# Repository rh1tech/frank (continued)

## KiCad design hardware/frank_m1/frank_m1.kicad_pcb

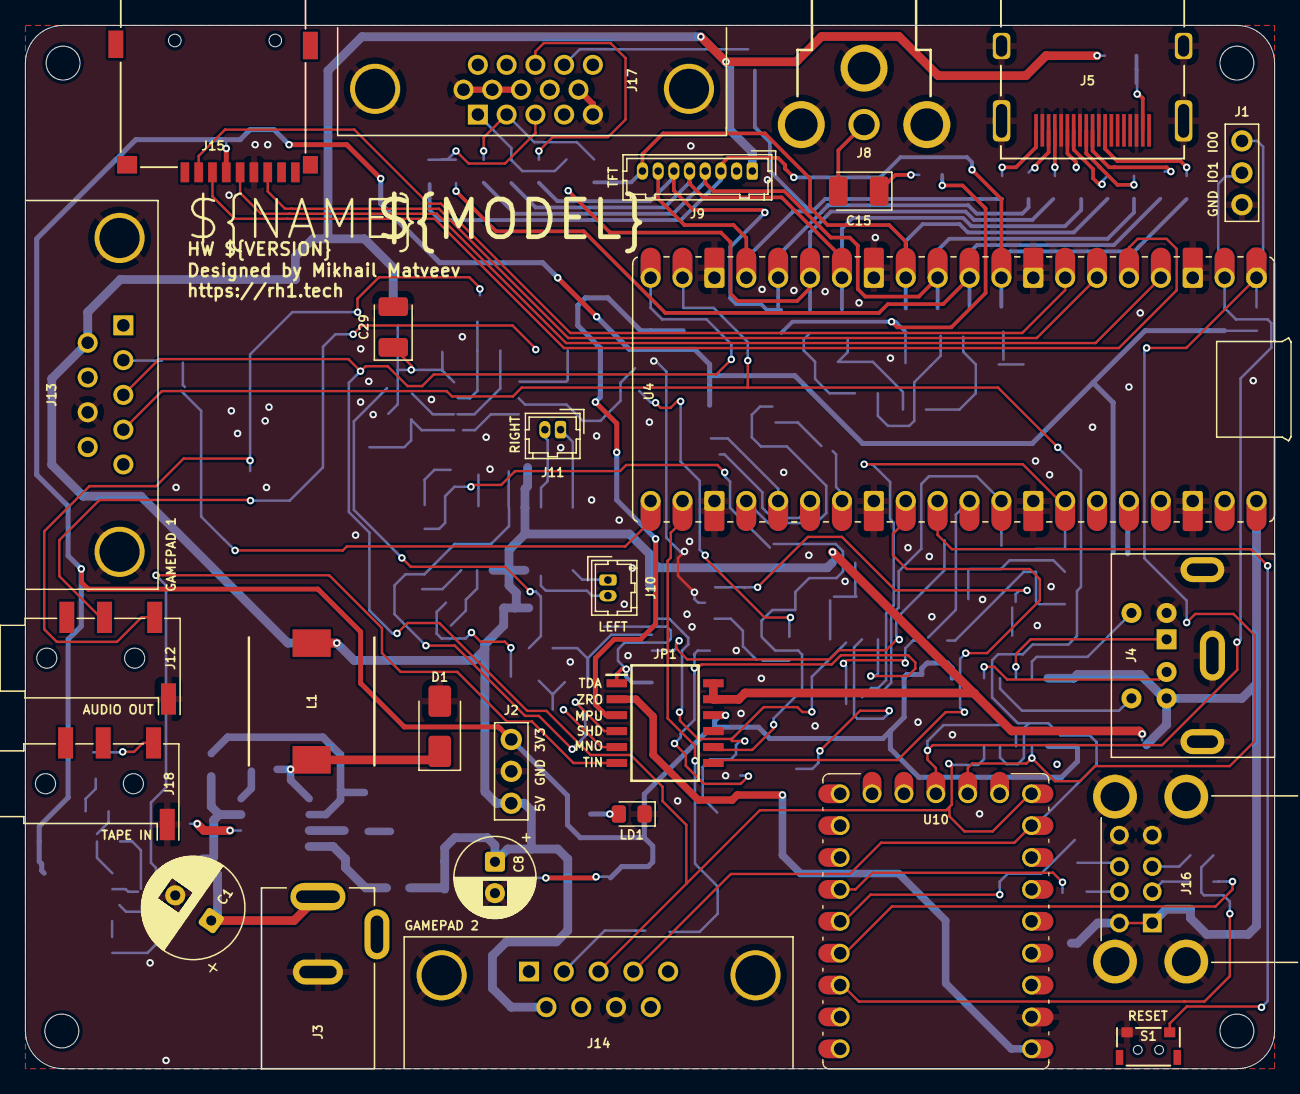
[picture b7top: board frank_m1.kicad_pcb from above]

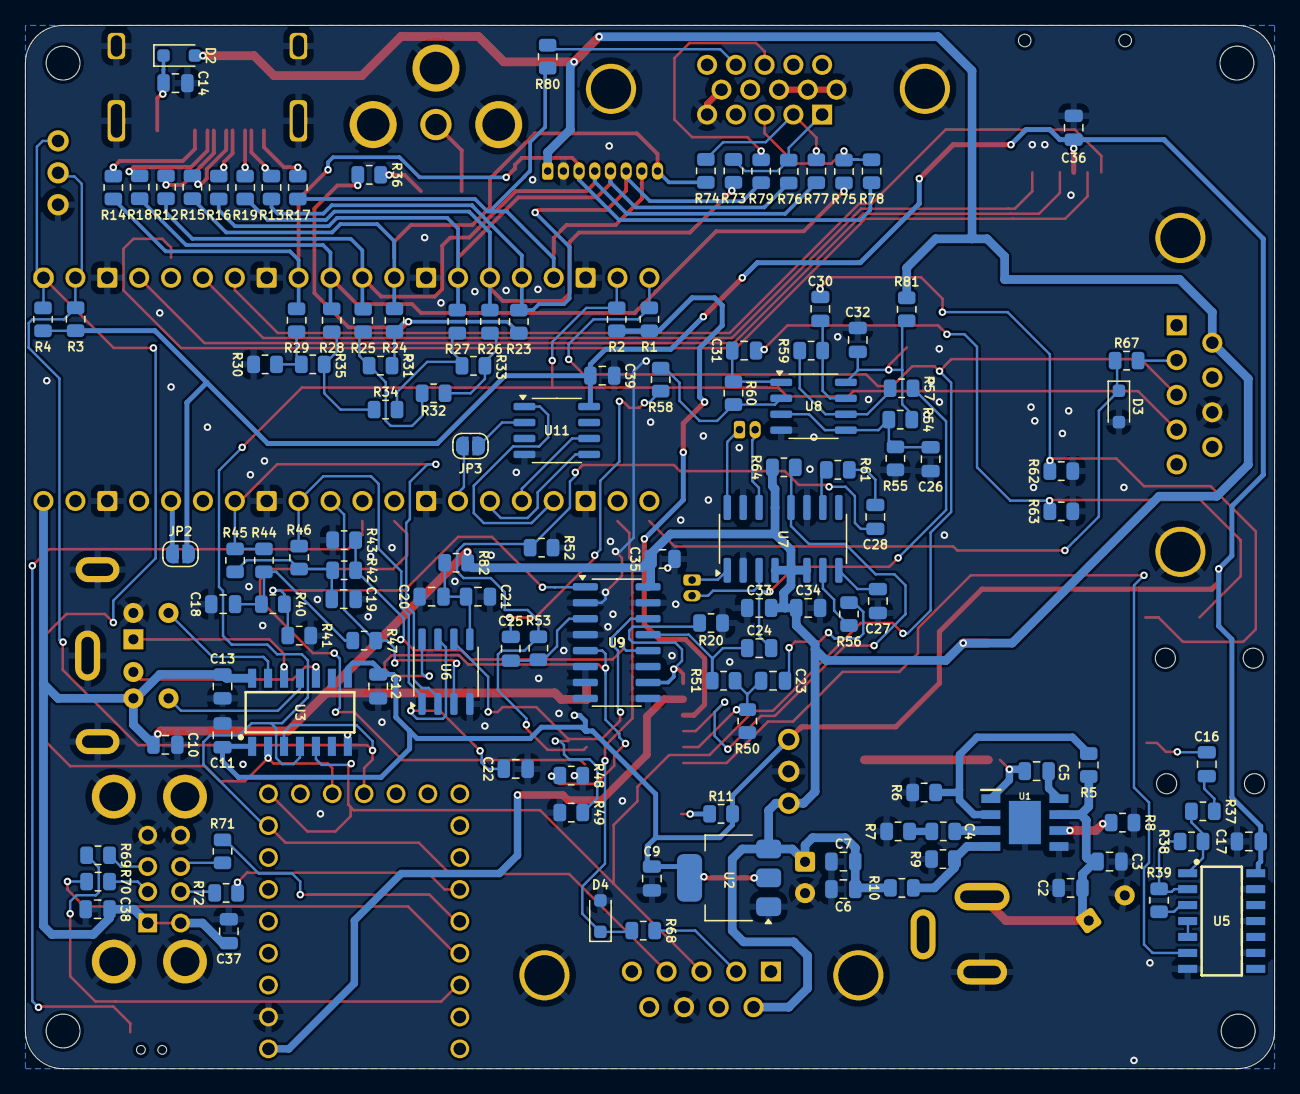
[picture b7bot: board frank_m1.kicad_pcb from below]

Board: 2 copper layers, 99.5 x 83.1 mm, 158 parts (127 on the bottom side), 119 nets.

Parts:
C1: 680u; Capacitor (Radial_D8.0mm_P3.50mm)
C2, C7, C9, C20, C22, C24, C25, C26, C30, C31, C37, C38: 10u; C_0805_2012Metric
C3, C5, C6, C10, C11, C12, C13, C14, C16, C17, C21, C27, C32, C35, C36, C39: 100n; C_0805_2012Metric
C4: 150pF; R_0805_2012Metric
C8: 220u; Capacitor (Radial_D6.3mm_P2.50mm)
C15: 220u; Capacitor (3528, tantalum, polar)
C18, C19: 47n; C_0805_2012Metric
C23, C28, C33: 1u; C_0805_2012Metric
C29: 10u; Capacitor (3528, tantalum, polar)
C34: 47u; C_0805_2012Metric
D1: 1N5822; D_SMA
D2: 1N5819WS; Diode (SOD-323)
D3, D4: 3V3; Diode (SOD-323)
H1, H2, H3, H4: Hole 2.7mm; Mounting Hole (2.7mm)
J1: UART; Pin Header (1x03)
J2: PWR; Pin Header (1x03)
J3: DC-005-5A-2.0; XKB_DC-005-5A-2.0
J4: MDC-036; MiniDIN (6 Pin, female)
J5: DC3RX19JA2; HDMI (female)
J8: RCA-103; RCJ-012
J9: Pin Header 1x08; Connector Female 1.25 JST 8P
J10: PAM L; Connector Female 1.25 JST 2P
J11: PAM R; Connector Female 1.25 JST 2P
J12, J18: PJ-320D; Jack (3.5mm, PJ-320D)
J13, J14: D-SUB 9 Male; D-SUB (9 pin, male, top mount)
J15: 104031-0811; MicroSD (SMD, long)
J16: SS-52100-004; USB Type A (stacked)
J17: D-SUB 15 Female; D-SUB (15 pin, female)
JP1: Main Jumpers; SOIC127P830X260-12N
JP2, JP3: Jumper (Solder); Jumper (solder)
L1: 22uH; CDRH104RNP
LD1: Green; LED (0805)
R1, R2, R3, R4, R20, R40, R42, R51, R53, R54, R55, R56, R57, R58, R61, R64: 10K; R_0805_2012Metric
R5, R7, R8, R38, R39: 100K; R_0805_2012Metric
R6: 24K; R_0805_2012Metric
R9: 8.2K; R_0805_2012Metric
R10: 43K; R_0805_2012Metric
R11, R46, R47, R67, R68, R76, R77, R78: 1K; R_0805_2012Metric
R12, R13, R14, R15, R16, R17, R18, R19, R24, R25, R26, R27, R28, R29: 270R; R_0805_2012Metric
R23: 750R; R_0805_2012Metric
R30: 300R; R_0805_2012Metric
R31, R32, R33, R34, R35: 150R; R_0805_2012Metric
R36: 51R; R_0805_2012Metric
R37: 4.7K; R_0805_2012Metric
R41, R43, R44, R45, R50, R52: 2K; R_0805_2012Metric
R48, R49: 470R; R_0805_2012Metric
R59, R60: 47K; R_0805_2012Metric
R62, R63: 20K; R_0805_2012Metric
R69, R70, R71, R72: 22R; R_0805_2012Metric
R73, R74, R75: 330R; R_0805_2012Metric
R79, R80, R81, R82: 100R; R_0805_2012Metric
S1: Reset RP2530A; TACT-SIDE-4623
U1: MP1584EN-LF-Z; SOIC127P600X170-9N
U2: AMS1117 3.3; SOT-223
U3: TXS0104EDR; SOIC127P600X175-14N
U4: Rasberry Pi Pico; Raspberry Pi Pico
U5: CD4069UBM; SOIC127P600X175-14N
U6: TDA1387T; SO-8
U7: PAM8403D; SOP-16
U8: LM358; SO-8
U9: 74HC4052D; SOP-16
U10: RP2040-Zero; Raspberry Pi Zero
U11: ESP-PSRAM32; SO-8

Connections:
+3V3: C9.1, C11.1, C12.1, C17.1, C36.2, C39.1, J2.1, J15.4 (VDD), JP1.10, JP2.2 (B), R3.2, R4.2, R11.2, U2.2 (VO), U3.1 (VCCA), U3.8 (OE), U5.14 (VDD), U11.8 (VCC)
/AMP_L: C24.1, R51.1, U9.13 (1Z)
/AMP_OUT_L: C30.2, J12.T, R62.2
/AMP_OUT_R: C31.2, J12.R, R63.2
/AMP_R: C25.1, R53.1, U9.3 (2Z)
/AUDIOSW: JP1.1, R20.2, U9.10 (S0)
/Audio/AMP_PAM_OUTL_M: J10.2, U7.3 (-OUTL)
/Audio/AMP_PAM_OUTL_P: J10.1, U7.1 (+OUT_L)
/Audio/AMP_PAM_OUTR_M: J11.2, U7.14 (-OUT_R)
/Audio/AMP_PAM_OUTR_P: J11.1, U7.16 (+OUT_R)
/Composite/CVBS: C15.2, J8.1
/EN: R5.1, R6.1, U1.2 (EN)
/LOAD_IN: JP1.6, U5.6 (I=*C)
/MONO_L: C23.1, JP1.5, R50.1, R51.2
/MONO_R: C28.1, JP1.8, R52.1, R53.2
/MSPUP3V3: JP1.3, R1.2, R2.2
/PGPIO0: J1.1, R4.1, U3.2 (A1), U4.1 (GPIO0), U10.13 (12)
/PGPIO1: J1.2, R3.1, U3.3 (A2), U4.2 (GPIO1), U10.12 (11)
/PGPIO2: J15.5 (CLK), U4.4 (GPIO2)
/PGPIO3: J15.3 (CMD), U4.5 (GPIO3)
/PGPIO4: J15.7 (DAT0), U4.6 (GPIO4)
/PGPIO5: J15.2 (DAT3/CD), U4.7 (GPIO5)
/PGPIO6: J9.3, R14.2, R29.1, R78.1, U4.9 (GPIO6)
/PGPIO7: R18.2, R28.1, R75.1, U4.10 (GPIO7)
/PGPIO8: J9.4, R12.2, R25.1, R77.1, U4.11 (GPIO8)
/PGPIO9: J9.8, R15.2, R24.1, R74.1, U4.12 (GPIO9)
/PGPIO10: J9.5, R16.2, R27.1, R76.1, U4.14 (GPIO10)
/PGPIO11: R19.2, R26.1, R73.1, U4.15 (GPIO11)
/PGPIO12: J9.6, R13.2, R23.1, R79.2, U4.16 (GPIO12)
/PGPIO13: J9.7, R17.2, R80.2, U4.17 (GPIO13)
/PGPIO14: J13.4, J14.4, R2.1, U3.4 (A3), U4.19 (GPIO14), U10.16 (15)
/PGPIO15: J13.3, J14.3, R1.1, U3.5 (A4), U4.20 (GPIO15), U10.15 (14)
/PGPIO16: D3.1 (K), R67.1, U4.21 (GPIO16)
/PGPIO17: D4.1 (K), R68.1, U4.22 (GPIO17)
/PGPIO18: U4.24 (GPIO18), U11.1 (~CE)
/PGPIO19: U4.25 (GPIO19), U11.6 (SCLK)
/PGPIO20: U4.26 (GPIO20), U11.5 (SI/SIO)
/PGPIO21: JP3.2 (B), U4.27 (GPIO21)
/PGPIO22: JP1.7, U4.29 (GPIO22)
/PGPIO26: R47.2, U4.31 (GPIO26_ADC0), U6.3 (DATA)
/PGPIO27: R46.2, U4.32 (GPIO27_ADC1), U6.1 (SCLK)
/PGPIO28: R44.1, R45.1, U4.34 (GPIO28_ADC2), U6.2 (LRCK)
/PRUN: S1.1, U4.30 (RUN)
/PS2/KB_CLK_5V: J4.5, U3.13 (B1)
/PS2/KB_DATA_5V: J4.1, U3.12 (B2)
/PS2/MS_CLK_5V: J4.6, U3.11 (B3)
/PS2/MS_DATA_5V: J4.2, U3.10 (B4)
/PWM_L: R42.2, R43.1, U9.12 (1Y0)
/PWM_R: R40.2, R41.1, U9.1 (2Y0)
/Power/VBUS_IN: C1.1, C2.1, C3.1, J3.1, R5.2, U1.7 (VIN)
/SHND: JP1.4, R64.2, U7.12 (SHND)
/TDA_L: R49.2, U6.6 (A_LEFT), U9.14 (1Y1)
/TDA_R: R48.1, U6.8 (A_RIGHT), U9.5 (2Y1)
/Tape In/TAPE: C16.2, J18.T
/ZGPIO2: R69.1, U10.3 (2)
/ZGPIO3: R70.1, U10.4 (3)
/ZGPIO4: R71.1, U10.5 (4)
/ZGPIO5: R72.1, U10.6 (5)
/Z_VBUS: JP1.2, U10.23 (5V)
GND: C1.2, C2.2, C3.2, C6.1, C7.2, C8.2, C9.2, C10.2, C11.2, C12.2, C13.2, C14.2, C17.2, C18.2, C19.2, C20.2, C21.2, C22.2, C26.1, C27.2, C29.2, C32.1, C33.2, C34.2, C35.1, C36.1, C37.2, C38.2, C39.2, D1.2 (A), D3.2 (A), D4.2 (A), J1.3, J2.2, J3.2, J4.3, J5.2 (G_D2), J5.5 (G_D1), J5.8 (G_D0), J5.11 (G_CLK), J5.17 (G_DDC/CEC), J5.20 (SHIELD1), J5.21 (SHIELD2), J5.22 (SHIELD3), J5.23 (SHIELD4), J8.2, J9.2, J12.S, J13.8, J14.8, J15.6 (VSS), J16.4 (GND1), J16.8 (GND2), J16.9 (Shield), J17.0, J17.5, J17.6, J17.7, J17.8, J17.10, J18.S, JP1.9, LD1.1 (K), R6.2, R7.2, R8.2, R9.1, R20.1, R30.1, R41.2, R43.2, R48.2, R49.1, R50.2, R52.2, R55.1, R62.1, R63.1, S1.2, U1.5 (GND), U1.9 (EP), U2.1 (GND), U3.7 (GND), U4.3 (GND), U4.8 (GND), U4.13 (GND), U4.18 (GND), U4.23 (GND), U4.28 (GND), U4.33 (AGND), U4.38 (GND), U5.7 (VSS), U5.9 (D14), U5.11 (E), U5.13 (F), U6.4 (AGND), U7.2 (PGND), U7.11 (GND), U7.15 (PGND), U8.4 (V-), U9.2 (2Y2), U9.4 (2Y3), U9.6 (~E), U9.7 (VEE), U9.8 (GND), U9.9 (S1), U9.11 (1Y3), U9.15 (1Y2), U10.22 (GND), U11.4 (VSS)
unnamed: C4.2, R7.1
unnamed: C15.1, R36.2
unnamed: C16.1, R37.2
unnamed: C18.1, R40.1, R44.2, R47.1
unnamed: C19.1, R42.1, R45.2, R46.1
unnamed: C23.2, R56.2
unnamed: C24.2, R57.2
unnamed: C25.2, R58.2
unnamed: C28.2, R61.2
unnamed: C30.1, R59.1, U8.7
unnamed: C31.1, R60.1, U8.1
unnamed: C5.2, D1.1 (K), L1.1, U1.1 (SW)
unnamed: C14.1, D2.1 (K), J5.18 (+5V)
unnamed: J5.12 (CLKN), R14.1
unnamed: J5.10 (CLKP), R18.1
unnamed: J5.9 (D0N), R12.1
unnamed: J5.7 (D0P), R15.1
unnamed: J5.6 (D1N), R16.1
unnamed: J5.4 (D1P), R19.1
unnamed: J5.3 (D2N), R13.1
unnamed: J5.1 (D2P), R17.1
unnamed: J13.2, R67.2
unnamed: J14.2, R68.2
unnamed: J16.3 (D1+), R69.2
unnamed: J16.2 (D1-), R70.2
unnamed: J16.7 (D2+), R71.2
unnamed: J16.6 (D2-), R72.2
unnamed: J17.1, R73.2, R76.2
unnamed: J17.2, R74.2, R77.2
unnamed: J17.3, R75.2, R78.2
unnamed: J17.13, R79.1
unnamed: J17.14, R80.1
unnamed: JP2.1 (A), U4.36 (3V3)
unnamed: JP3.1 (A), U11.2 (SO/SIO)
unnamed: LD1.2 (A), R11.1
unnamed: R23.2, R24.2, R31.2, R36.1
unnamed: R25.2, R31.1, R32.2
unnamed: R26.2, R32.1, R33.2
unnamed: R27.2, R33.1, R34.2
unnamed: R28.2, R34.1, R35.2
unnamed: R29.2, R30.2, R35.1
unnamed: C5.1, U1.8 (BST)
unnamed: C4.1, U1.3 (COMP)
unnamed: R9.2, R10.2, U1.4 (FB)
unnamed: R8.1, U1.6 (FREQ)
unnamed: R37.1, R38.2, U5.1 (A)
unnamed: R39.1, U5.3 (B)
unnamed: U5.4 (H=*B), U5.5 (C)
unnamed: R38.1, R39.2, U5.2 (G-*A)
unnamed: C22.1, U6.7 (FLT)
unnamed: C20.1, C21.1, R82.1, U6.5 (VA)
unnamed: R56.1, U7.7 (INL)
unnamed: R61.1, U7.10 (INR)
unnamed: C27.1, U7.8 (VREF)
unnamed: C26.2, R54.1, R55.2, U8.3 (+), U8.5 (+)
unnamed: R58.1, R60.2, U8.2 (-)
unnamed: R57.1, R59.2, U8.6 (-)
unnamed: C29.1, C32.2, R54.2, R81.2, U8.8 (V+)
VBUS: C6.2, C7.1, C8.1, C10.1, C13.1, C33.1, C34.1, C35.2, C37.1, C38.1, D2.2 (A), J2.3, J4.4, J9.1, J13.6, J14.6, J16.1 (VBUS1), J16.5 (VBUS2), JP1.11, JP1.12, L1.2, R10.1, R64.1, R81.1, R82.2, U2.3 (VI), U3.14 (VCCB), U4.40 (VBUS), U7.4 (PVDD), U7.5 (MUTE), U7.6 (VDD), U7.13 (PVDD), U9.16 (VCC)
